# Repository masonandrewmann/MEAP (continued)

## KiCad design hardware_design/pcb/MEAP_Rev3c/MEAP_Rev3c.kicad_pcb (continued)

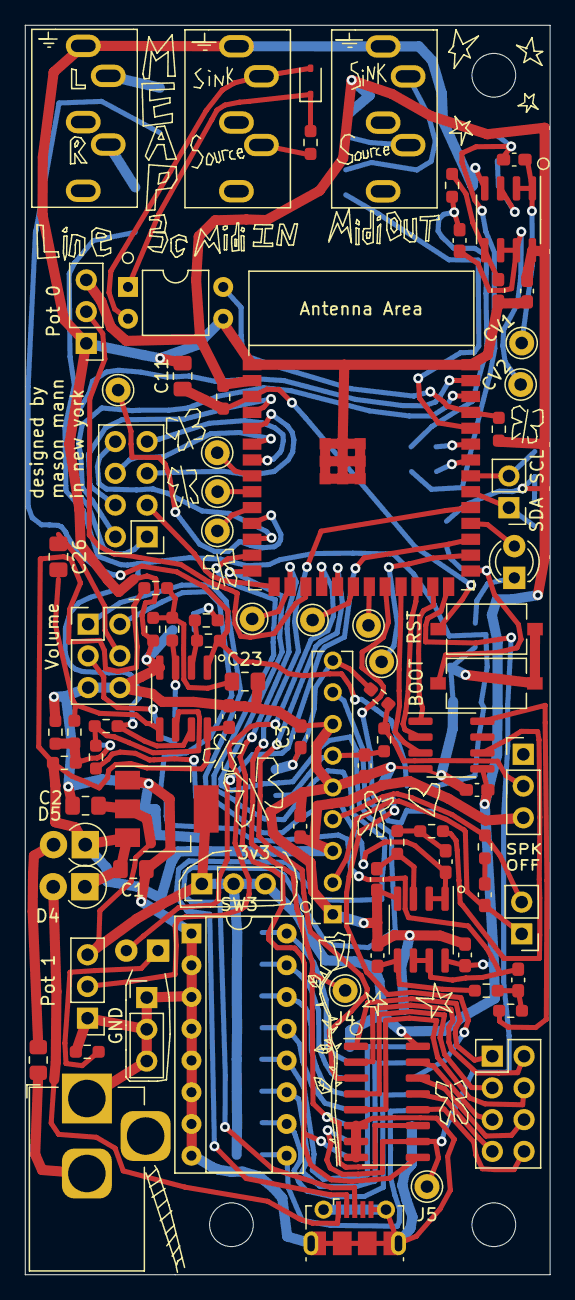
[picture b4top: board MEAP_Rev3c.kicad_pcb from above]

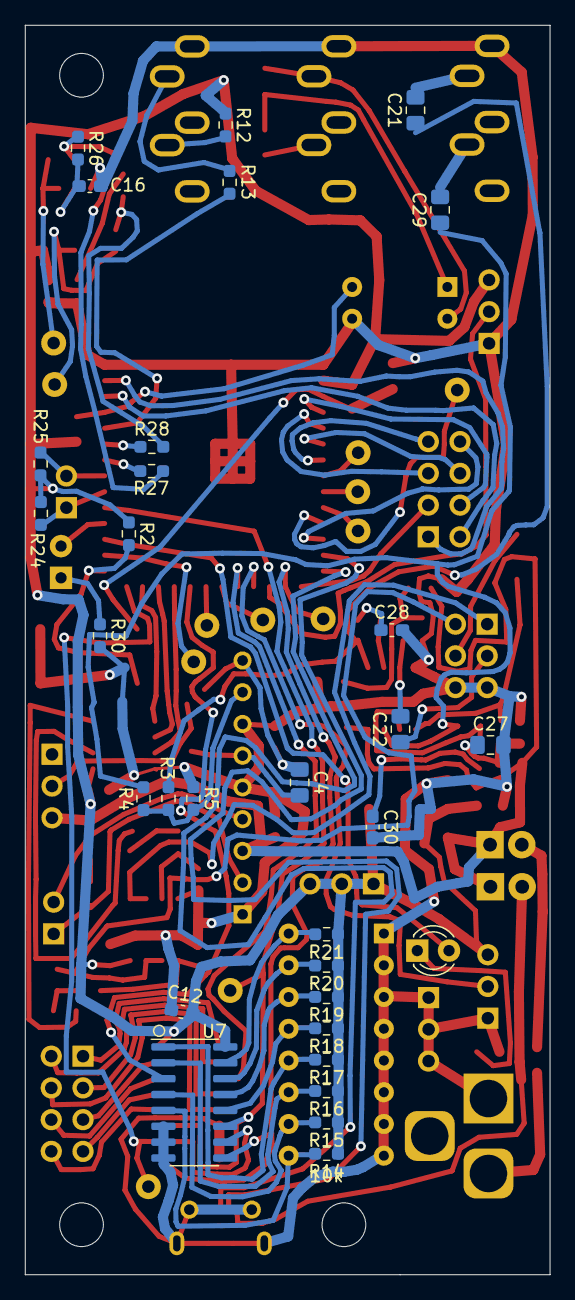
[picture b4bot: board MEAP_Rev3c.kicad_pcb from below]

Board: 2 copper layers, 42.0 x 100.0 mm, 117 parts (31 on the bottom side), 101 nets.

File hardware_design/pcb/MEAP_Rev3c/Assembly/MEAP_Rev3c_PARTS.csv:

Designator,Comment,Footprint,LCSC
"C1, C4, C21, C29",10u,Capacitor_SMD:C_0805_2012Metric_Pad1.18x1.45mm_HandSolder,C89832
"C3, C5",10n,Capacitor_SMD:C_0603_1608Metric_Pad1.08x0.95mm_HandSolder,C57112
C6,220n,Capacitor_SMD:C_0603_1608Metric_Pad1.08x0.95mm_HandSolder,C21120
"C7, C9",1000p,Capacitor_SMD:C_0603_1608Metric_Pad1.08x0.95mm_HandSolder,C1588
"C8, C10",470p,Capacitor_SMD:C_0603_1608Metric_Pad1.08x0.95mm_HandSolder,C1620
"C11, C22, C23, C26, C27",1u,Capacitor_SMD:C_0805_2012Metric_Pad1.18x1.45mm_HandSolder,C354368
"C12, C13, C14, C15, C16, C17, C18, C19, C20, C24",100n,Capacitor_SMD:C_0603_1608Metric_Pad1.08x0.95mm_HandSolder,C14663
"C28, C30",1p,Capacitor_SMD:C_0603_1608Metric_Pad1.08x0.95mm_HandSolder,C115062
D1,1N4148,Diode_SMD:D_SOD-323,C2128
FB1,FB,Inductor_SMD:L_0805_2012Metric_Pad1.15x1.40mm_HandSolder,C1017
J17,USB_B_Micro,Connector_USB:USB_Micro-B_Molex-105017-0001,C136000
"R1, R30",330,Resistor_SMD:R_0603_1608Metric_Pad0.98x0.95mm_HandSolder,C23138
"R2, R11, R14, R15, R16, R17, R18, R19, R20, R21, R26, R27, R28, R29",10k,Resistor_SMD:R_0603_1608Metric_Pad0.98x0.95mm_HandSolder,C25804
"R3, R4",100k,Resistor_SMD:R_0603_1608Metric_Pad0.98x0.95mm_HandSolder,C25803
R5,20k,Resistor_SMD:R_0603_1608Metric_Pad0.98x0.95mm_HandSolder,C4184
"R7, R8, R9, R10",7k5,Resistor_SMD:R_0603_1608Metric_Pad0.98x0.95mm_HandSolder,C23234
"R12, R13",47,Resistor_SMD:R_0603_1608Metric_Pad0.98x0.95mm_HandSolder,C23182
"R22, R23",220,Resistor_SMD:R_0603_1608Metric_Pad0.98x0.95mm_HandSolder,C22962
"R24, R25",1k,Resistor_SMD:R_0603_1608Metric_Pad0.98x0.95mm_HandSolder,C21190
"R31, R32, R33, R34, R37, R40",1000,Resistor_SMD:R_0603_1608Metric_Pad0.98x0.95mm_HandSolder,C21190
"R35, R36",50k,Resistor_SMD:R_0603_1608Metric_Pad0.98x0.95mm_HandSolder,C25819
"R38, R41",100,Resistor_SMD:R_0603_1608Metric_Pad0.98x0.95mm_HandSolder,C22775
"R39, R42",68,Resistor_SMD:R_0603_1608Metric_Pad0.98x0.95mm_HandSolder,C27592
U1,MCP6002-xMC,Package_SO:SOIC-8_3.9x4.9mm_P1.27mm,C7377
U2,LM1117-3.3,Package_TO_SOT_SMD:SOT-223,C23984
U3,MCP6002-xSN,Package_SO:SOIC-8_3.9x4.9mm_P1.27mm,C7377
U5,PT8211,Package_SO:SOIC-8_3.9x4.9mm_P1.27mm,C5260468
"U6, U7",4051,Package_SO:SOIC-16_3.9x9.9mm_P1.27mm,C21379
U8,ESP32-S3-WROOM-1,PCM_Espressif:ESP32-S3-WROOM-1,C2913202
U9,NE5532,Package_SO:SOIC-8_3.9x4.9mm_P1.27mm,C7426

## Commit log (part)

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2023-08-29 added test example
2023-08-29 Added hardware test
2023-08-29 cleaned up Hardware_Test
2023-08-29 renamed hardwaretest
2023-08-29 added template
2023-08-29 added sequencer example
2023-08-29 added touch keybord example
2023-09-02 changed pins for pt8211
2023-09-02 examples update
2023-09-03 added env example
2023-09-05 added photos
2023-09-26 added demo code
2023-10-09 added several examples
2023-10-10 improved FM example
2023-10-10 added descriptions to examples
2023-10-16 added env and seq examples
2023-10-18 hardware+generative example
2023-10-23 added examples
2023-10-23 updated examples
2023-10-23 cleaned up example
2023-10-30 cleaned up chord seq
2023-10-30 added sample examples
2023-10-30 added spiegel example
2023-10-30 cleaned up spiegel example
2023-10-30 added piano sample
2023-11-06 added ryoji ikeda examples
2023-11-06 fixed ikeda bug
2023-11-14 examples added
2023-11-14 fixed sequencer example
2023-11-14 sequencer example fixed
2023-11-18 added basic ImC example
2023-11-20 added new random functions and examples
2023-11-20 added filter example
2023-11-27 added granular example
2023-12-04 added some fresh programs
2023-12-19 rev3
2024-02-03 meap update
2024-02-07 meap3 examples
2024-03-06 lots of updates eek
2024-04-22 added meap library
2024-04-22 updated documentation
2024-06-18 lots of stuff
2024-06-24 meap
2024-06-24 test commit
2024-06-24 another test commit
2024-07-26 big cleanup
2024-08-01 library updates for meap rev3
2024-08-14 removed my extra code, updated library to support MEAP Rev4
2024-08-14 cleaned up basic examples
2024-08-14 /DS_Store removed
2024-08-14 cleaned up old examples
2024-08-14 remove DS_Store
2024-08-14 added python conversion scripts
2024-08-14 removed vscode settings directory
2024-08-14 restructured directories
2024-09-06 lots of changes eek
2024-09-16 updated examples and tutorials
2024-09-16 fixed basic template
2024-09-16 fixed template
2024-09-23 new wavetables, code cleanup, more examples and tutorials
2024-09-23 tutorial 8 updated to 16bit
2024-09-30 bug fixes
2024-09-30 removed duplicate file
2024-09-30 filled out remainder of midi note table
2024-10-01 bugfix
2024-10-07 some bug fixes and new tutorials
2024-10-07 tutorial/example fixes
2024-10-14 fixed midi template
2024-10-15 bug fixes on mOperator, mOscil and mWavetable
2024-10-28 new tutorials and some adjustments to granular classes
2024-11-05 added mEventDelayMicros
2024-11-05 mEventDelayMicros cleanup
2024-11-07 added drum sequencing tutorial
2024-11-07 updated drum sequencing tutorial
2024-11-21 added mSample reverse, etc
2024-11-21 mSample bugfix
2024-11-21 another mSample bugfix
2024-12-03 updated board partition
2025-01-24 hardware updates
2025-02-20 big update
2025-03-06 new dsp functions added
2025-04-24 refactoring
2025-05-14 filepath typo
2025-07-13 added function pointers to mMML
2025-07-16 removed hardware files from repo
2025-07-16 removed hardware files
2025-07-16 removed .gitignore
2025-07-16 rearranged filestructure
2025-08-11 added initial support for meapv4c, implemented cap1280 support
2025-08-11 moved meap_classes definitions to header; library is now fully header-only
2025-08-11 rearranged files
2025-08-20 reorganizing
2025-09-02 added analogdelay and refactoring
2025-09-06 naming conventions
2025-09-08 cleaned up tutorials
2025-09-08 cleaning up tutorials
2025-09-08 updated templates
2025-09-14 re-added meap board definitions
2025-09-15 volume control
2025-09-22 added mTransitionTable class
2025-09-22 updated mTransitionTable
2025-10-06 QOL improvements to mOscil and mSample, mStringSynth bug fixed
2025-10-15 mOperator and mSample fixes
2025-10-15 fixed typo in readme
2025-10-21 fixed mFM4Instrument setGain function
2025-10-28 added extra examples folder and mBitcrusher constructor
2025-10-28 mGrainCloud bugfixes
2025-11-21 added midi support and voice steal polyphony to mRompler
2026-03-11 envelope cleanup, stringinstrument fix, added mSyncOsc and mAnalogInstrument
2026-03-11 mAnalogInstrument bugfix
2026-06-16 instrument improvements, new wavetables/windows, moved to new esp32-arduino touch api as required
